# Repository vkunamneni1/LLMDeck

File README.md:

# LLMDeck
LLMDeck is an 8 key macropad with a rotary encoder for temperature control, an OLED display, and 3 RGB LEDs for status, all in a 3D-printed 2 part case. 

It runs on a XIAO RP2040 with KMK firmware to prompt multiple LLMs, utilizing them for various everyday tasks.

## Features
- XIAO RP2040 running on KMK firmware
- 3 keys to switch between 3 different LLMs (ChatGPT, Gemini, Llama)
- 3 keys to either summarize, lengthen, or humanize clipboard text
- 2 keys to open corresponding LLM chatbot in browser
- EC11 rotary encoder to adjust prompt temperature (0.0 - 1.0)
- 128×32 0.91" OLED Display (displays current LLM/function)
- 3 RGB LEDs displaying whether LLMDeck is powered on
- 3D-printed case designed in **Onshape**
- Silkscreen of many LLMS and Hack Club!

## Overall CAD Model

Made in Onshape w/ models from Grabcad

## PCB
### Schematic

(also featured on back of PCB!)

### PCB Design
#### With filled zone

#### Without filled zone

### 3D PCB Design
#### Front

#### Back

## Case
### Top

### Bottom

(complete assembly at top of README)

## Firmware
All firmware was developed in VSCode (w/ KMK). FIRMWARE IS UNTESTED AND WILL PROBABLY NOT WORK. API keys are not included yet (I will add them when I assemble LLMDeck).
- API calls to OpenAI, Google, Meta to utilize LLM functions
- WIFI connection needed
- Data stored in tmp directory
- UNTESTED

## BOM
- 1x Seeed XIAO RP2040
- 9x Through-hole 1N4148 Diodes
- 8x MX-Style switches
- 1x EC11 Rotary encoders
- 1x 0.91 inch OLED display
- 8x Blank DSA keycaps
- 3x SK6812 MINI-E LEDs
- 4x M3x5mx4mm heatset inserts
- 4x M3x16mm screws
- 3D Printed Case (top and bottom)

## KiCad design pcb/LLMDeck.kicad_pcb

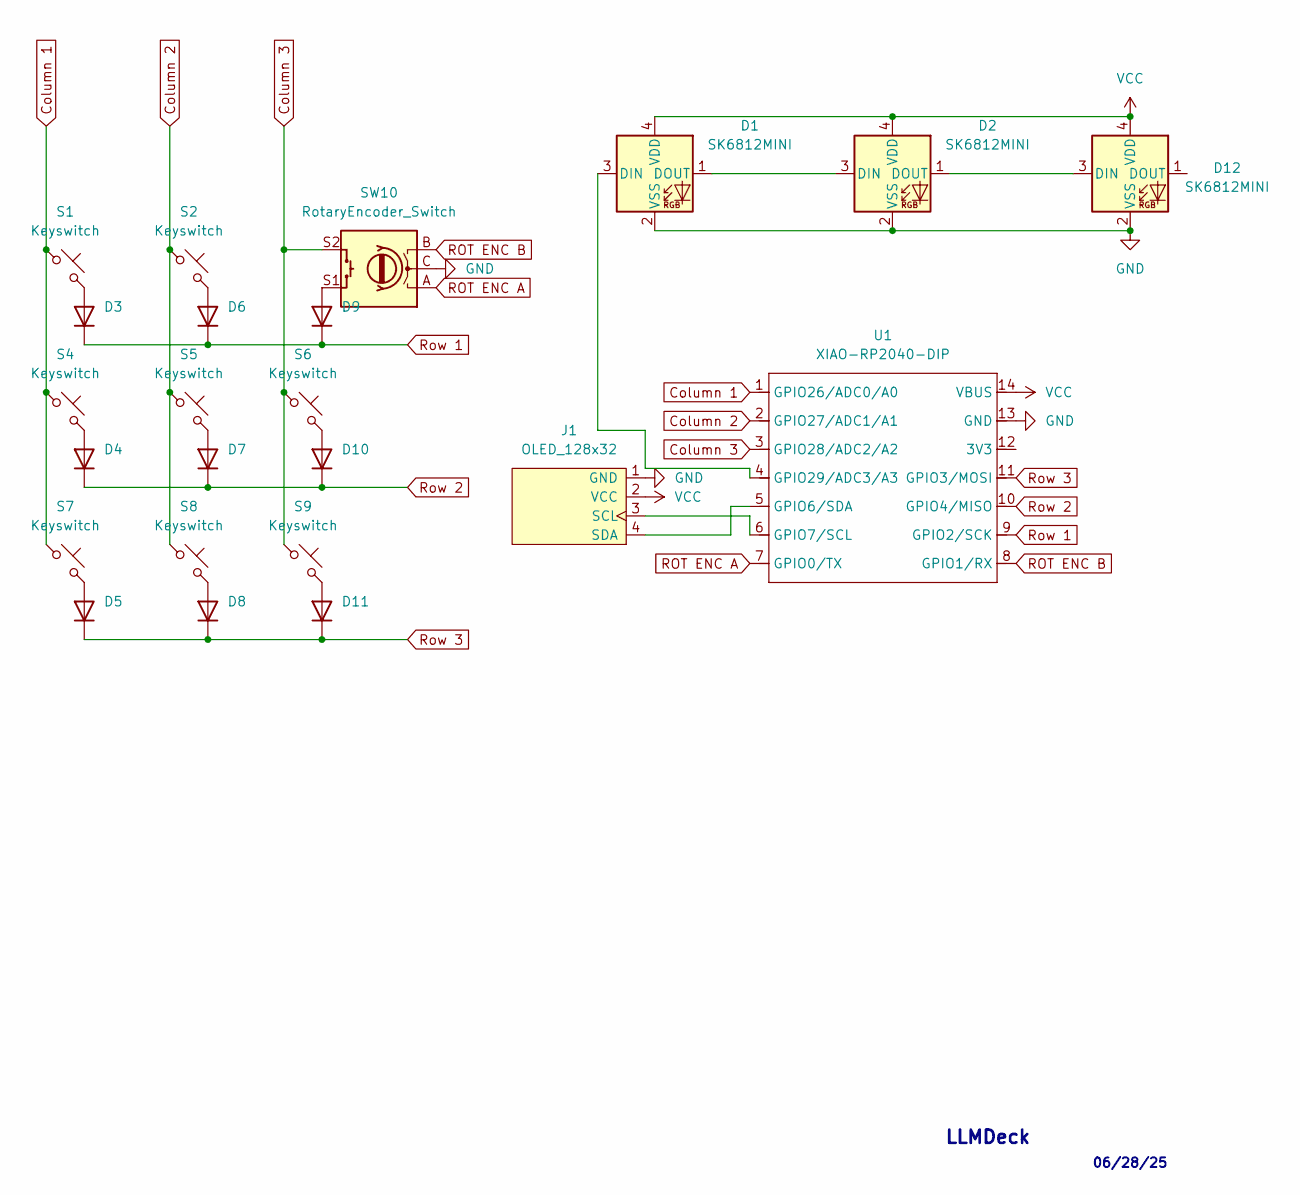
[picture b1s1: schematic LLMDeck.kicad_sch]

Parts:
D1, D2, D12: SK6812MINI; LED_SK6812MINI_PLCC4_3.5x3.5mm_P1.75mm
D3, D4, D5, D6, D7, D8, D9, D10, D11: 1N4148; D_DO-35_SOD27_P7.62mm_Horizontal
J1: OLED_128x32; SSD1306-0.91-OLED-4pin-128x32
S1, S2, S4, S5, S6, S7, S8, S9: Keyswitch; SW_Cherry_MX_1.00u_PCB
SW10: RotaryEncoder_Switch; RotaryEncoder_Alps_EC11E-Switch_Vertical_H20mm
U1: XIAO-RP2040-DIP

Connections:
Column 1: S1.1, S4.1, S7.1, U1.1 (GPIO26/ADC0/A0)
Column 2: S2.1, S5.1, S8.1, U1.2 (GPIO27/ADC1/A1)
Column 3: S6.1, S9.1, SW10.S2, U1.3 (GPIO28/ADC2/A2)
GND: D1.2 (VSS), D2.2 (VSS), D12.2 (VSS), J1.1 (GND), SW10.C, U1.13 (GND)
unnamed: D1.3 (DIN), U1.4 (GPIO29/ADC3/A3)
unnamed: D1.1 (DOUT), D2.3 (DIN)
unnamed: D3.2 (A), S1.2
unnamed: D4.2 (A), S4.2
unnamed: D5.2 (A), S7.2
unnamed: D6.2 (A), S2.2
unnamed: D7.2 (A), S5.2
unnamed: D8.2 (A), S8.2
unnamed: D9.2 (A), SW10.S1
unnamed: D10.2 (A), S6.2
unnamed: D11.2 (A), S9.2
unnamed: D2.1 (DOUT), D12.3 (DIN)
unnamed: J1.3 (SCL), U1.6 (GPIO7/SCL)
unnamed: J1.4 (SDA), U1.5 (GPIO6/SDA)
ROT ENC A: SW10.A, U1.7 (GPIO0/TX)
ROT ENC B: SW10.B, U1.8 (GPIO1/RX)
Row 1: D3.1 (K), D6.1 (K), D9.1 (K), U1.9 (GPIO2/SCK)
Row 2: D4.1 (K), D7.1 (K), D10.1 (K), U1.10 (GPIO4/MISO)
Row 3: D5.1 (K), D8.1 (K), D11.1 (K), U1.11 (GPIO3/MOSI)
VCC: D1.4 (VDD), D2.4 (VDD), D12.4 (VDD), J1.2 (VCC), U1.14 (VBUS)

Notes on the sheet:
06/28/25
LLMDeck

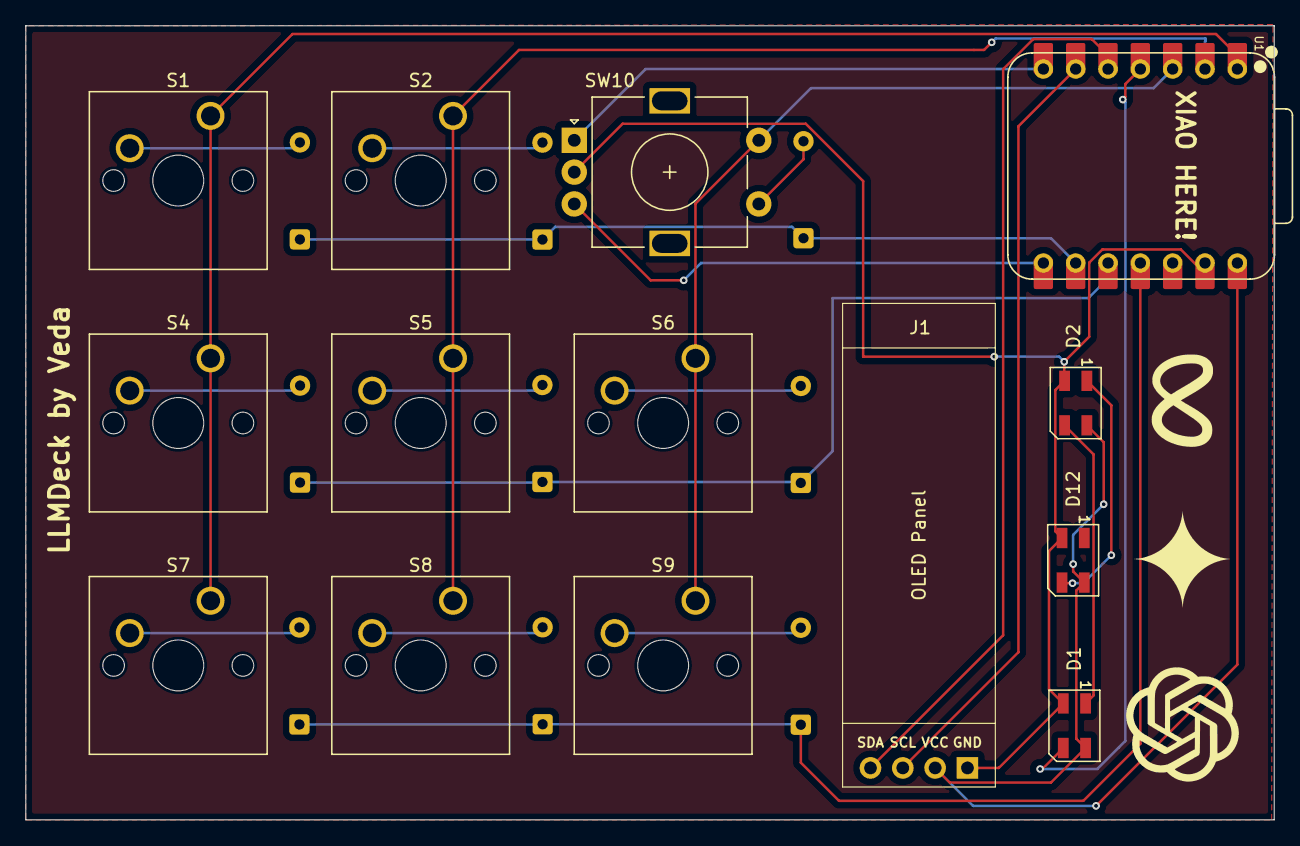
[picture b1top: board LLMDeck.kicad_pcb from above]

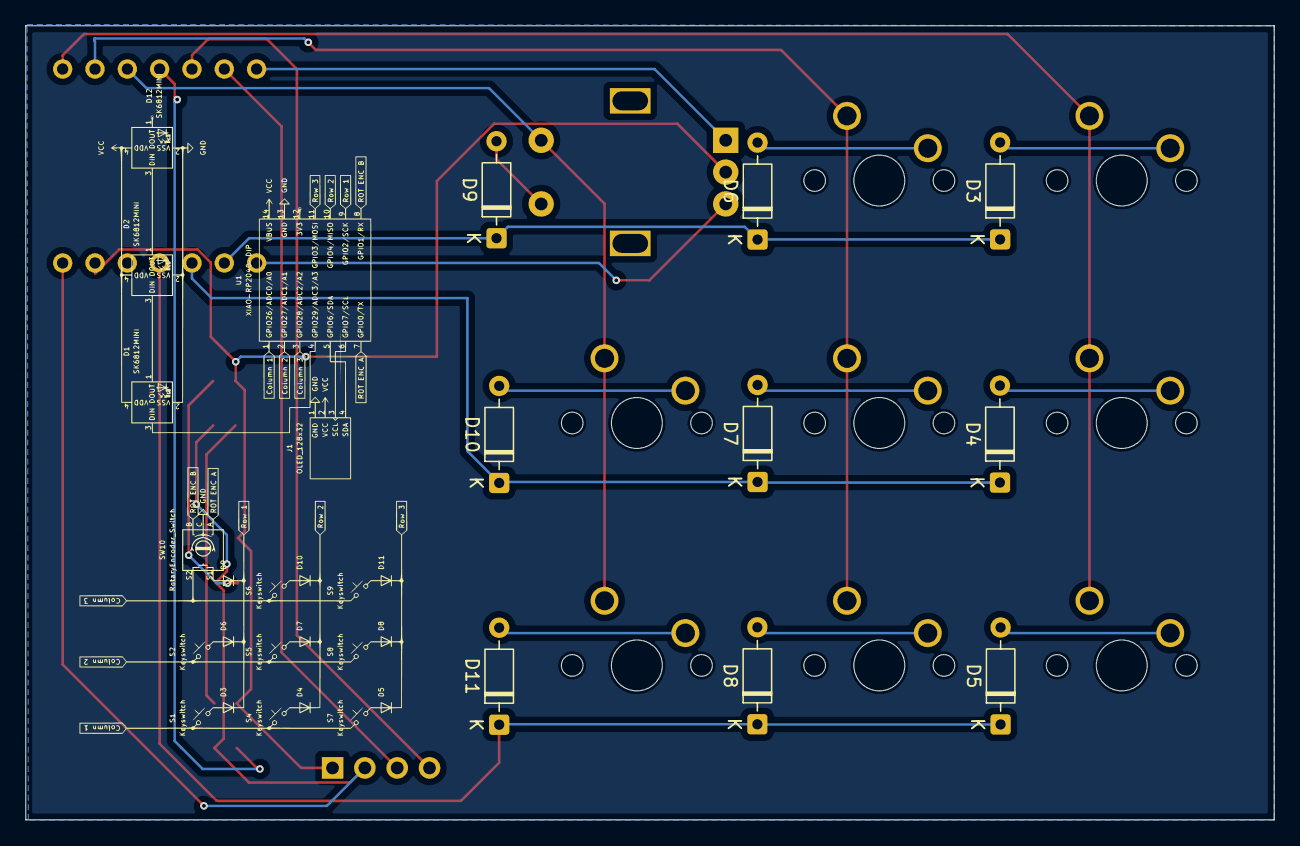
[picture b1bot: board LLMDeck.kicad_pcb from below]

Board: 2 copper layers, 98.1 x 62.4 mm, 24 parts (9 on the bottom side), 24 nets.

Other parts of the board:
G: LOGO

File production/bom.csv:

Designator,Footprint,Quantity,Value,LCSC Part #
"D1, D12, D2",LED_SK6812MINI_PLCC4_3.5x3.5mm_P1.75mm,3,SK6812MINI,
"D10, D11, D3, D4, D5, D6, D7, D8, D9",D_DO-35_SOD27_P7.62mm_Horizontal,9,1N4148,
J1,SSD1306-0.91-OLED-4pin-128x32,1,OLED_128x32,
"S1, S2, S4, S5, S6, S7, S8, S9",SW_Cherry_MX_1.00u_PCB,8,Keyswitch,
SW10,RotaryEncoder_Alps_EC11E-Switch_Vertical_H20mm,1,RotaryEncoder_Switch,
U1,XIAO-RP2040-DIP,1,XIAO-RP2040-DIP,

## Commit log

2025-06-29 schem + pcb design completed
2025-06-29 hackpad src files added
